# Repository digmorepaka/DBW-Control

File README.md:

# Drive by wire controller

## For bench use, testing use, stationary engine use, offroad use, and completely without warranty or liability from me or any of the contributors

## Features:

* UI over Serial
* PID Closed loop control
* Configurable TPS and APP calibration, stored in local EEPROM
* Configurable 3 point Non-linear APP to TPS relation
* EEPROM intergrity checksum
* Multiple throttle states(idle, transient, stable, safety) to improve behavior
* Non-linear 3 point TPS and APP position sensor failure detection
* Semi-automatic failsafe correlation calibration
* Safety mode

## TODO:
* (Off)road test
* Automatic TPS1/TPS2 and APP1/APP2 failsafe correlation calibration
* Increase TPS vs APP configurable cell count
* Voltage compensation
* Improve HW
* Throttle smoothing/delay
* Get to understand parts of the code that I don't undestand :P
* Improve UI, possibly integrate with TunerStudio
* Code cleanup and optimization

## Dependencies:
* frankboesing/FastCRC
* br3ttb/PID
* greygnome/EnableInterrupt
* robtillaart/MultiMap

## Hardware
Designed and ordered a test board

Currently testing with an Arduino UNO and a H bridge. H bridge is configured with a TC4424 driver and a NOT gate as to have a **single direction select pin, and a 5th enable/disable MOSFET**. TC4425/4428 is a better choice because it doesn't needan inverter due to it's mix of inverting/non inverting drivers. This is what I had on hand.

Currently testing with a **Toyota DENSO 89281-52021 Pedal and 22030-0D010 ThrottleBody** from a 2004-2009 Corolla Verso 1ZZ-FE. 2002+ MR2/Celica uses something similar. In the future I will also be working with Kawasaki Versys 1000 2015+ Individual **Mikuni 6307120 throttlebodies**.

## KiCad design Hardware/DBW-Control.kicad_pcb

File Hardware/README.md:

# Hardware

## Initial test board

### Goals:
* Completely standalone
* Core stability and safety features
* Fully featured for current software
* Screw terminals
* Easily debugable

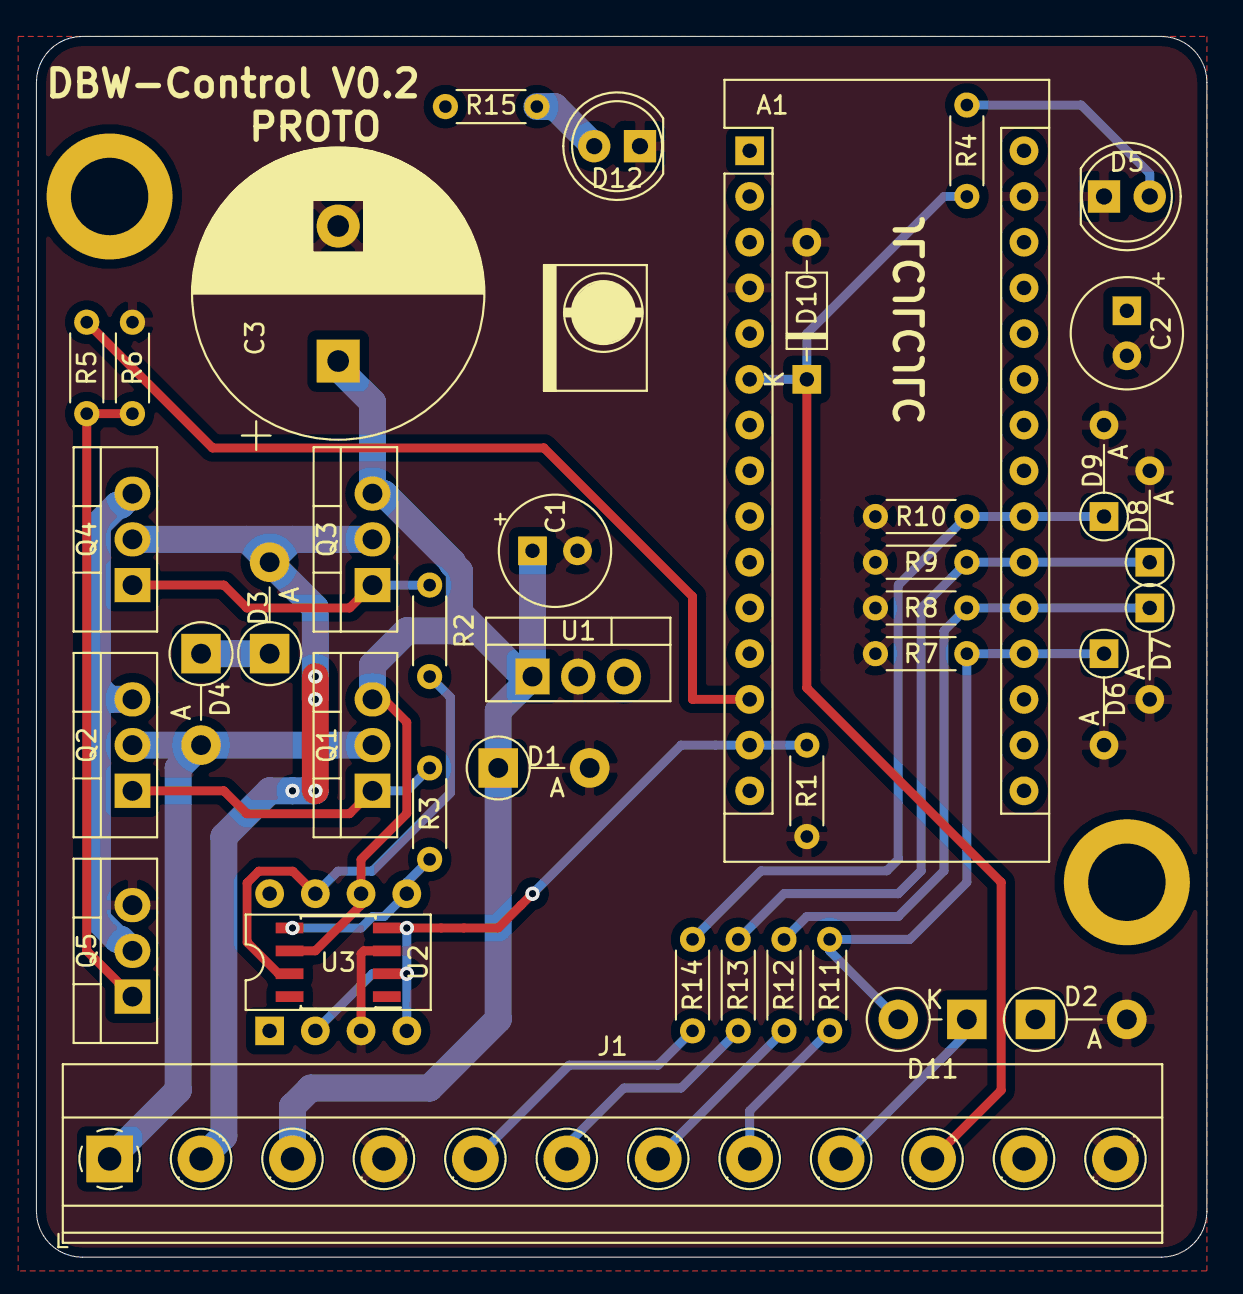
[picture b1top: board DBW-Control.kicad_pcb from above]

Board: 2 copper layers, 65.0 x 67.8 mm, 40 parts (0 on the bottom side), 26 nets.

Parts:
A1: Arduino_Nano_v3.x; Arduino_Nano
C1: 10u; CP_Radial_Tantal_D6.0mm_P2.50mm
C2: 47u; CP_Radial_Tantal_D6.0mm_P2.50mm
C3: 3300u; CP_Radial_D16.0mm_P7.50mm
D1, D3, D4: 20V; D_DO-41_SOD81_P5.08mm_Vertical_AnodeUp
D2: 1N5339B 5V6; D_DO-41_SOD81_P5.08mm_Vertical_AnodeUp
D5, D12: LED; LED_D5.0mm
D6, D7, D8, D9: 5V1; D_DO-35_SOD27_P5.08mm_Vertical_AnodeUp
D10: 5V1; D_DO-35_SOD27_P7.62mm_Horizontal
D11: 1N4004; D_DO-41_SOD81_P3.81mm_Vertical_KathodeUp
J1: Conn_01x12_Female; TerminalBlock_Phoenix_MKDS-1,5-12-5.08_1x12_P5.08mm_Horizon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
Q1, Q3: IRF9540N; TO-220-3_Vertical
Q2, Q4, Q5: IRF540N; TO-220-3_Vertical
R1, R5: 1K; R_Axial_DIN0204_L3.6mm_D1.6mm_P5.08mm_Horizontal
R2, R3: 75R; R_Axial_DIN0204_L3.6mm_D1.6mm_P5.08mm_Horizontal
R4, R15: 330R; R_Axial_DIN0204_L3.6mm_D1.6mm_P5.08mm_Horizontal
R6: 180R; R_Axial_DIN0204_L3.6mm_D1.6mm_P5.08mm_Horizontal
R7, R8, R9, R10: 100K; R_Axial_DIN0204_L3.6mm_D1.6mm_P5.08mm_Horizontal
R11, R12, R13, R14: 470R; R_Axial_DIN0204_L3.6mm_D1.6mm_P5.08mm_Horizontal
U1: LM2940T; TO-220-3_Vertical
U2: TC4425; DIP-8_W7.62mm
U3: TC4425; SOIC-8_3.9x4.9mm_P1.27mm

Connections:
+5V: A1.27, C2.1, D2.1, J1.11, R15.1, U1.3
+12V: C1.1, C3.1, D1.1, J1.3, Q1.3, Q3.3, U1.1, U2.6, U3.6
ERROR_LED: A1.6, D10.1, J1.10, R4.2
GND: A1.4, A1.29, C1.2, C2.2, C3.2, D1.2, D2.2, D5.1, D6.2, D7.2, D8.2, D9.2, D10.2, D12.1, J1.4, J1.12, Q5.3, R1.2, R5.2, R7.1, R8.1, R9.1, R10.1, U1.2, U2.3, U3.3
HB_DIR: A1.14, R1.1, U2.2, U2.4, U3.2, U3.4
HB_PWM: A1.13, R6.1
M+: D4.2, J1.2, Q3.2, Q4.2
M-: D3.2, J1.1, Q1.2, Q2.2
unnamed: A1.19, D6.1, D11.2, R7.2, R11.2
unnamed: A1.20, D7.1, R8.2, R12.2
unnamed: A1.21, D8.1, R9.2, R13.2
unnamed: A1.22, D9.1, R10.2, R14.2
unnamed: D3.1, D4.1
unnamed: D5.2, R4.1
unnamed: D12.2, R15.2
unnamed: Q1.1, Q2.1, R3.1
unnamed: Q2.3, Q4.3, Q5.2
unnamed: Q3.1, Q4.1, R2.1
unnamed: Q5.1, R5.1, R6.2
unnamed: R2.2, U2.7, U3.7
unnamed: R3.2, U2.5, U3.5
POT_PEDAL: J1.6, R13.1
POT_PEDAL2: J1.5, R14.1
POT_THROTTLE: J1.8, R11.1
POT_THROTTLE2: J1.7, R12.1
TPS: D11.1, J1.9

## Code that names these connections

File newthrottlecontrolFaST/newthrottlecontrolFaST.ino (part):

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void serialRead(byte);

// Inputs
const int POT_THROTTLE = A0; // Servo Position Input
const int POT_THROTTLE2 = A1; // Servo Position Input2
const int POT_PEDAL = A3; // Pedal Sensor Input
const int POT_PEDAL2 = A2; // Pedal Sensor Input
const int POT_IDLE = A4; //Requested Idle Input
const byte idlePWMPin = 2;

// Pins H bridge
const byte HB_DIRECTION = 11; // H bridge Direction
const byte HB_PWM = 10;     // H bridge PWM (speed)

// Throttle constraints, max voltages in both direction
 int MinTPS;
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
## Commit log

2022-04-21 fix direction
2022-04-21 whoops
2022-04-21 Create LICENSE,md
2022-04-21 Rename LICENSE,md to LICENSE.md
2022-04-22 safety check
2022-04-25 Basic safety mode, improved safety mapping
2022-04-25 Rename newthrottlecontrolFaST/newthrottlecontrolFaST.ino to src/DBW-Control.ino
2022-04-25 Rename newthrottlecontrolFaST/ETC.h to src/ETC.h
2022-04-26 Add Initial hardware
2022-05-11 Automatic calibration

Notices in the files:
newthrottlecontrolFaST/newthrottlecontrolFaST.ino:
Licensed under the GPL v3
Copyright (C) Norman Paulino
modify it under the terms of the GNU General Public License
